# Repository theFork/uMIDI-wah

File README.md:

# uMIDI-wah

An optical guitar wah circuit based on the weeping demon circuit

* Uses [uMIDI](https://github.com/theFork/uMIDI) for control, MIDI and USB communication
* Optical wah control using a PWM

## uMIDI attachment
In order to be able to mount a uMIDI on top of the board, the three uMIDI GPIO connectors (boxed headers) have to be placed on its bottom side. Also, a male pin header row (1x10 pins, 2.54mm) has to be soldered to the MIDI and power section of the uMIDI module (also bottom side).

Another option would be to attach the uMIDI below the wah PCBA. In this case, the connectors have to side on the top side of the PCB.

In both cases, female headers are required for the wah PCBA:

* 3x Female header 2x5 pins, 2.54mm (i.e. TE 215307-5)
* 1x Female header 1x10 pins, 2.54mm (i.e. TE 1-215297-0)

## EDA
* Requires KiCad 8.x.x

## Ressources
Many of this is based on the work of Chet Gnegy: https://ccrma.stanford.edu/~chet/projects/weepingdemon.html

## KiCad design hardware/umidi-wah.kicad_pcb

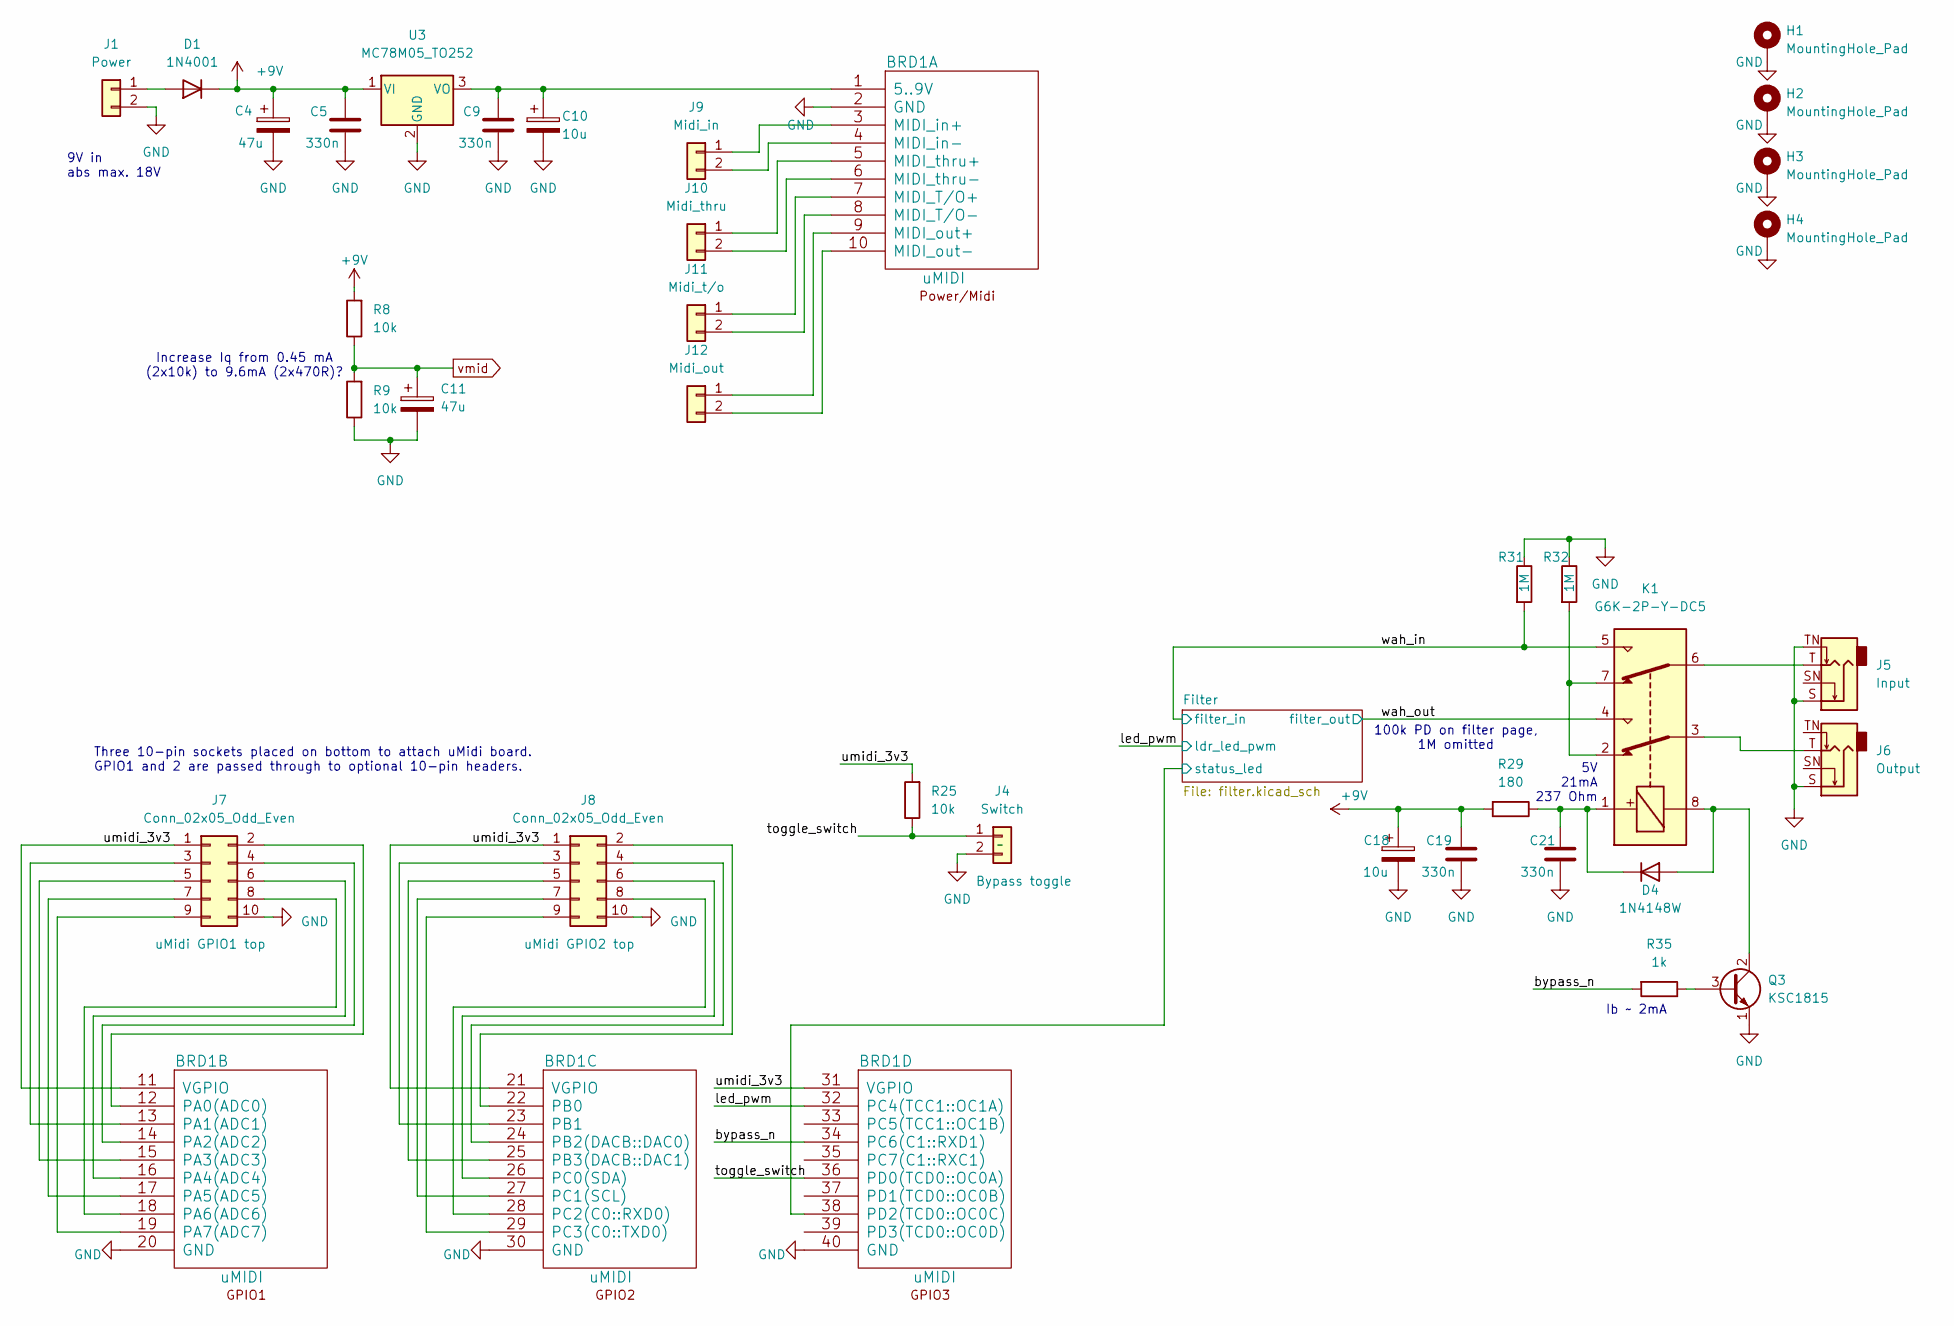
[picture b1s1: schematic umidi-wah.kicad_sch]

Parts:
BRD1: uMIDI; uMIDI_faceup
C4, C11: 47u; C_1206_3216Metric_Pad1.33x1.80mm_HandSolder
C5, C9, C19, C21: 330n; C_0805_2012Metric_Pad1.18x1.45mm_HandSolder
C10, C18: 10u; C_1206_3216Metric_Pad1.33x1.80mm_HandSolder
D1: 1N4001; D_DO-41_SOD81_P10.16mm_Horizontal
D4: 1N4148W; D_SOD-123
H1, H2, H3, H4: MountingHole_Pad; MountingHole_3.2mm_M3_Pad
J1: Power; SolderWire-1sqmm_1x02_P5.4mm_D1.4mm_OD2.7mm
J4: Switch; SolderWire-1sqmm_1x02_P5.4mm_D1.4mm_OD2.7mm
J5: Input; Jack_6.35mm_Neutrik_NMJ4HCD2_Horizontal
J6: Output; Jack_6.35mm_Neutrik_NMJ4HCD2_Horizontal
J7, J8: Conn_02x05_Odd_Even; IDC-Header_2x05_P2.54mm_Vertical
J9: Midi_in; SolderWire-1sqmm_1x02_P5.4mm_D1.4mm_OD2.7mm
J10: Midi_thru; SolderWire-1sqmm_1x02_P5.4mm_D1.4mm_OD2.7mm
J11: Midi_t/o; SolderWire-1sqmm_1x02_P5.4mm_D1.4mm_OD2.7mm
J12: Midi_out; SolderWire-1sqmm_1x02_P5.4mm_D1.4mm_OD2.7mm
K1: G6K-2P-Y-DC5; Relay_DPDT_Omron_G6K-2P-Y; Manufacturer Part Number G6K-2P-Y-DC5
Q3: KSC1815; TO-92; Manufacturer Part Number KSC1815
R8, R9, R25: 10k; R_0805_2012Metric_Pad1.20x1.40mm_HandSolder
R29: 180; R_0805_2012Metric_Pad1.20x1.40mm_HandSolder
R31, R32: 1M; R_0805_2012Metric_Pad1.20x1.40mm_HandSolder
R35: 1k; R_0805_2012Metric_Pad1.20x1.40mm_HandSolder
U3: MC78M05_TO252; TO-252-2; Manufacturer Part Number MC78M05CD

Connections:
+9V: C4.1, C5.1, C18.1, C19.1, D1.1 (K), R8.2, R29.2, U3.1 (VI); also elsewhere on the board
/Filter/status_led: BRD1.38 (PD2(TCD0::OC0C)); also elsewhere on the board
/bypass_n: BRD1.34 (PC6(C1::RXD1)), R35.2
/led_pwm: BRD1.32 (PC4(TCC1::OC1A)); also elsewhere on the board
/toggle_switch: BRD1.36 (PD0(TCD0::OC0A)), J4.1, R25.1
/umidi_3v3: BRD1.11 (VGPIO), BRD1.21 (VGPIO), BRD1.31 (VGPIO), J7.1, J8.1, R25.2
/wah_in: K1.5, R31.2; also elsewhere on the board
/wah_out: K1.4; also elsewhere on the board
GND: BRD1.2 (GND), BRD1.20 (GND), BRD1.30 (GND), BRD1.40 (GND), C4.2, C5.2, C9.2, C10.2, C11.2, C18.2, C19.2, C21.2, H1.1, H2.1, H3.1, H4.1, J1.2, J4.2, J5.S, J5.TN, J6.S, J7.10, J8.10, Q3.1 (E), R9.1, R31.1, R32.1, U3.2 (GND); also elsewhere on the board
unnamed: BRD1.1 (5..9V), C9.1, C10.1, U3.3 (VO)
unnamed: BRD1.7 (MIDI_T/O+), J11.1
unnamed: BRD1.8 (MIDI_T/O-), J11.2
unnamed: BRD1.3 (MIDI_in+), J9.1
unnamed: BRD1.4 (MIDI_in-), J9.2
unnamed: BRD1.9 (MIDI_out+), J12.1
unnamed: BRD1.10 (MIDI_out-), J12.2
unnamed: BRD1.5 (MIDI_thru+), J10.1
unnamed: BRD1.6 (MIDI_thru-), J10.2
unnamed: BRD1.12 (PA0(ADC0)), J7.2
unnamed: BRD1.13 (PA1(ADC1)), J7.3
unnamed: BRD1.14 (PA2(ADC2)), J7.4
unnamed: BRD1.15 (PA3(ADC3)), J7.5
unnamed: BRD1.16 (PA4(ADC4)), J7.6
unnamed: BRD1.17 (PA5(ADC5)), J7.7
unnamed: BRD1.18 (PA6(ADC6)), J7.8
unnamed: BRD1.19 (PA7(ADC7)), J7.9
unnamed: BRD1.22 (PB0), J8.2
unnamed: BRD1.23 (PB1), J8.3
unnamed: BRD1.24 (PB2(DACB::DAC0)), J8.4
unnamed: BRD1.25 (PB3(DACB::DAC1)), J8.5
unnamed: BRD1.26 (PC0(SDA)), J8.6
unnamed: BRD1.27 (PC1(SCL)), J8.7
unnamed: BRD1.28 (PC2(C0::RXD0)), J8.8
unnamed: BRD1.29 (PC3(C0::TXD0)), J8.9
unnamed: D1.2 (A), J1.1
unnamed: D4.2 (A), K1.8, Q3.2 (C)
unnamed: C21.1, D4.1 (K), K1.1, R29.1
unnamed: J5.T, K1.6
unnamed: J6.T, K1.3
unnamed: K1.2, K1.7, R32.2
unnamed: Q3.3 (B), R35.1
vmid: C11.1, R8.1, R9.2; also elsewhere on the board

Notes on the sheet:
Increase Iq from 0.45 mA (2x10k) to 9.6mA (2x470R)?
9V in abs max. 18V
Ib ~ 2mA
Three 10-pin sockets placed on bottom to attach uMidi board. GPIO1 and 2 are passed through to optional 10-pin headers.
100k PD on filter page, 1M omitted
5V 21mA 237 Ohm

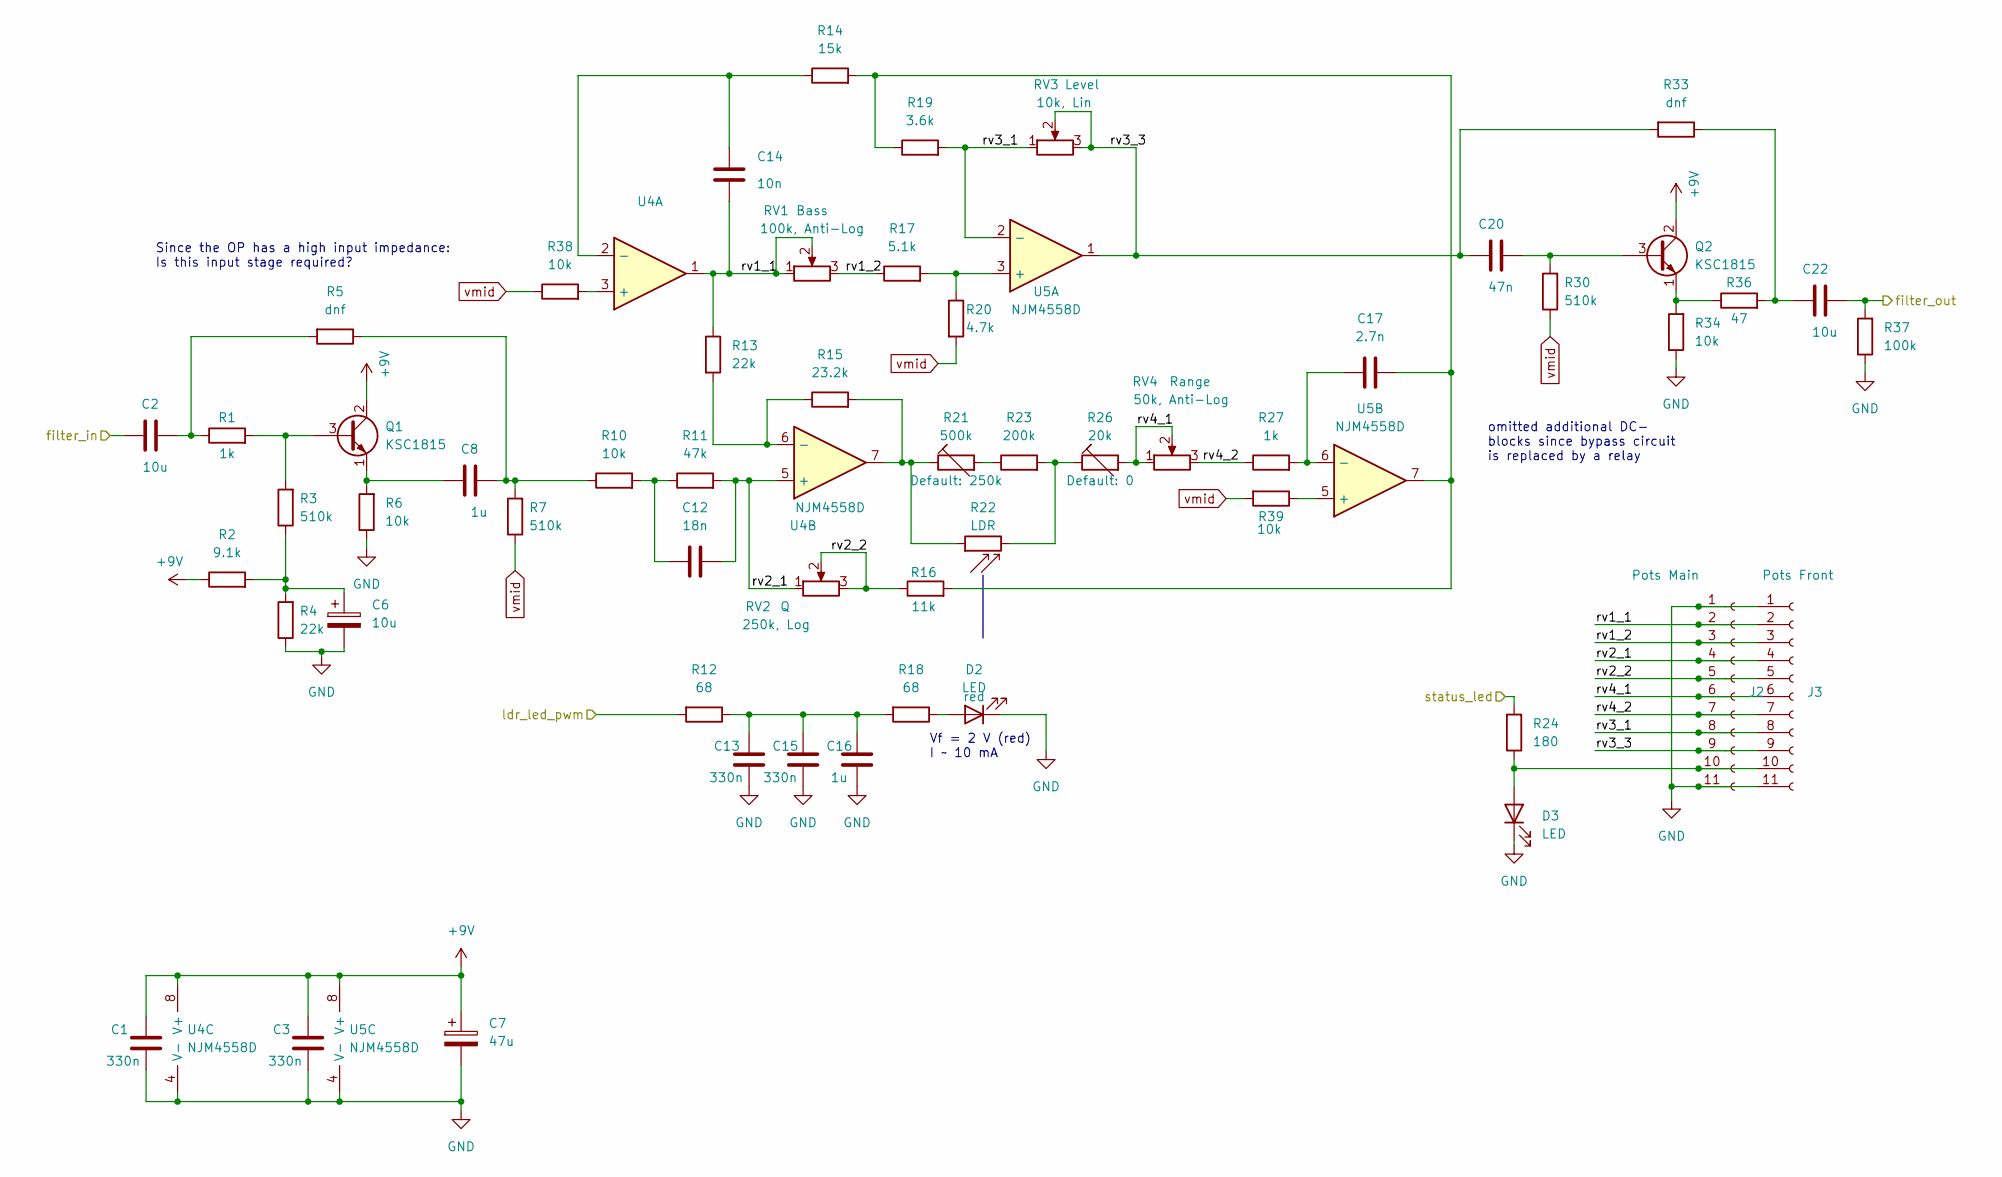
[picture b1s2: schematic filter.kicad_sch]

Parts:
C1, C3, C13, C15: 330n; C_0805_2012Metric_Pad1.18x1.45mm_HandSolder
C2, C22: 10u; C_Rect_L7.2mm_W11.0mm_P5.00mm_FKS2_FKP2_MKS2_MKP2
C6: 10u; C_1206_3216Metric_Pad1.33x1.80mm_HandSolder
C7: 47u; C_1206_3216Metric_Pad1.33x1.80mm_HandSolder
C8: 1u; C_Rect_L4.6mm_W5.5mm_P2.50mm_MKS02_FKP02
C12: 18n; C_Rect_L7.0mm_W2.5mm_P5.00mm
C14: 10n; C_Rect_L4.6mm_W5.5mm_P2.50mm_MKS02_FKP02; Manufacturer Part Number MKS0C021000B00JSSD
C16: 1u; C_0805_2012Metric_Pad1.18x1.45mm_HandSolder
C17: 2.7n; C_Rect_L7.0mm_W2.5mm_P5.00mm
C20: 47n; C_Rect_L4.6mm_W5.5mm_P2.50mm_MKS02_FKP02; Manufacturer Part Number MKS0C024700B00JSSD
D2, D3: LED; LED_D5.0mm
J2: Pots Main; PinHeader_1x11_P2.54mm_Vertical
J3: Pots Front; PinHeader_1x11_P2.54mm_Vertical
Q1, Q2: KSC1815; TO-92; Manufacturer Part Number KSC1815
R1, R27: 1k; R_0805_2012Metric_Pad1.20x1.40mm_HandSolder
R2: 9.1k; R_0805_2012Metric_Pad1.20x1.40mm_HandSolder
R3, R7, R30: 510k; R_0805_2012Metric_Pad1.20x1.40mm_HandSolder
R4, R13: 22k; R_0805_2012Metric_Pad1.20x1.40mm_HandSolder
R5, R33: dnf; R_0805_2012Metric_Pad1.20x1.40mm_HandSolder
R6, R10, R34, R38, R39: 10k; R_0805_2012Metric_Pad1.20x1.40mm_HandSolder
R11: 47k; R_0805_2012Metric_Pad1.20x1.40mm_HandSolder
R12, R18: 68; R_0805_2012Metric_Pad1.20x1.40mm_HandSolder
R14: 15k; R_0805_2012Metric_Pad1.20x1.40mm_HandSolder
R15: 23.2k; R_0805_2012Metric_Pad1.20x1.40mm_HandSolder
R16: 11k; R_0805_2012Metric_Pad1.20x1.40mm_HandSolder
R17: 5.1k; R_0805_2012Metric_Pad1.20x1.40mm_HandSolder
R19: 3.6k; R_0805_2012Metric_Pad1.20x1.40mm_HandSolder
R20: 4.7k; R_0805_2012Metric_Pad1.20x1.40mm_HandSolder
R21: 500k; Potentiometer_Piher_PT-10-V10_Vertical_Hole; Manufacturer Part Number PT10LV10-504A2020
R22: LDR; R_LDR_4.9x4.2mm_P2.54mm_Vertical; Manufacturer Part Number PDV P9004 or PDV 9203
R23: 200k; R_0805_2012Metric_Pad1.20x1.40mm_HandSolder
R24: 180; R_0805_2012Metric_Pad1.20x1.40mm_HandSolder
R26: 20k; Potentiometer_Piher_PT-10-V10_Vertical_Hole; Manufacturer Part Number PT10LV10-203A2020
R36: 47; R_0805_2012Metric_Pad1.20x1.40mm_HandSolder
R37: 100k; R_0805_2012Metric_Pad1.20x1.40mm_HandSolder
RV1: 100k, Anti-Log; Potentiometer_Alpha_RV16AF-20-15k-Single_Horizontal; Manufacturer Part Number RV16AF-20-15K-C100K
RV2: 250k, Log; Potentiometer_Alpha_RV16AF-20-15k-Single_Horizontal; Manufacturer Part Number RV16AF-20-15K-A250K
RV3: 10k, Lin; Potentiometer_Alpha_RV16AF-20-15k-Single_Horizontal; Manufacturer Part Number RV16AF-20-15K-B10K
RV4: 50k, Anti-Log; Potentiometer_Alpha_RV16AF-20-15k-Single_Horizontal; Manufacturer Part Number RV16AF-20-15K-C50K
U4, U5: NJM4558D; DIP-8_W7.62mm_Socket_LongPads; Manufacturer Part Number NJM4558D

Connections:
+9V: C1.1, C3.1, C7.1, Q1.2 (C), Q2.2 (C), R2.1, U4.8 (V+), U5.8 (V+); also elsewhere on the board
/Filter/rv1_1: C14.2, J2.2, J3.2, R13.1, RV1.1, RV1.2, U4.1
/Filter/rv1_2: J2.3, J3.3, R17.1, RV1.3
/Filter/rv2_1: C12.2, J2.4, J3.4, R11.2, RV2.1, U4.5 (+)
/Filter/rv2_2: J2.5, J3.5, R16.1, RV2.2, RV2.3
/Filter/rv3_1: J2.8, J3.8, R19.2, RV3.1, U5.2 (-)
/Filter/rv3_3: C20.1, J2.9, J3.9, R33.2, RV3.2, RV3.3, U5.1
/Filter/rv4_1: J2.6, J3.6, R26.2, RV4.1, RV4.2
/Filter/rv4_2: J2.7, J3.7, R27.1, RV4.3
/Filter/status_led: R24.2; also elsewhere on the board
/led_pwm: R12.2; also elsewhere on the board
/wah_in: C2.1; also elsewhere on the board
/wah_out: C22.2, R37.2; also elsewhere on the board
GND: C1.2, C3.2, C6.2, C7.2, C13.2, C15.2, C16.2, D2.1 (K), D3.1 (K), J2.1, J2.11, J3.1, J3.11, R4.1, R6.1, R34.1, R37.1, U4.4 (V-), U5.4 (V-); also elsewhere on the board
unnamed: C2.2, R1.1, R5.2
unnamed: C6.1, R2.2, R3.1, R4.2
unnamed: C8.2, R5.1, R7.2, R10.1
unnamed: C12.1, R10.2, R11.1
unnamed: C13.1, C15.1, C16.1, R12.1, R18.2
unnamed: C17.2, R14.2, R16.2, R19.1, U5.7
unnamed: C22.1, R33.1, R36.2
unnamed: D2.2 (A), R18.1
unnamed: D3.2 (A), J2.10, J3.10, R24.1
unnamed: Q1.3 (B), R1.2, R3.2
unnamed: C8.1, Q1.1 (E), R6.2
unnamed: C20.2, Q2.3 (B), R30.2
unnamed: Q2.1 (E), R34.2, R36.1
unnamed: R15.2, R21.1, R22.1, U4.7
unnamed: R21.2, R23.1
unnamed: R22.2, R23.2, R26.1
unnamed: R38.2, U4.3 (+)
unnamed: C14.1, R14.1, U4.2 (-)
unnamed: R13.2, R15.1, U4.6 (-)
unnamed: R17.2, R20.1, U5.3 (+)
unnamed: R39.1, U5.5 (+)
unnamed: C17.1, R27.2, U5.6 (-)
vmid: R7.1, R20.2, R30.1, R38.1, R39.2; also elsewhere on the board

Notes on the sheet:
omitted additional DC- blocks since bypass circuit is replaced by a relay
Vf = 2 V (red) I ~ 10 mA
Since the OP has a high input impedance: Is this input stage required?

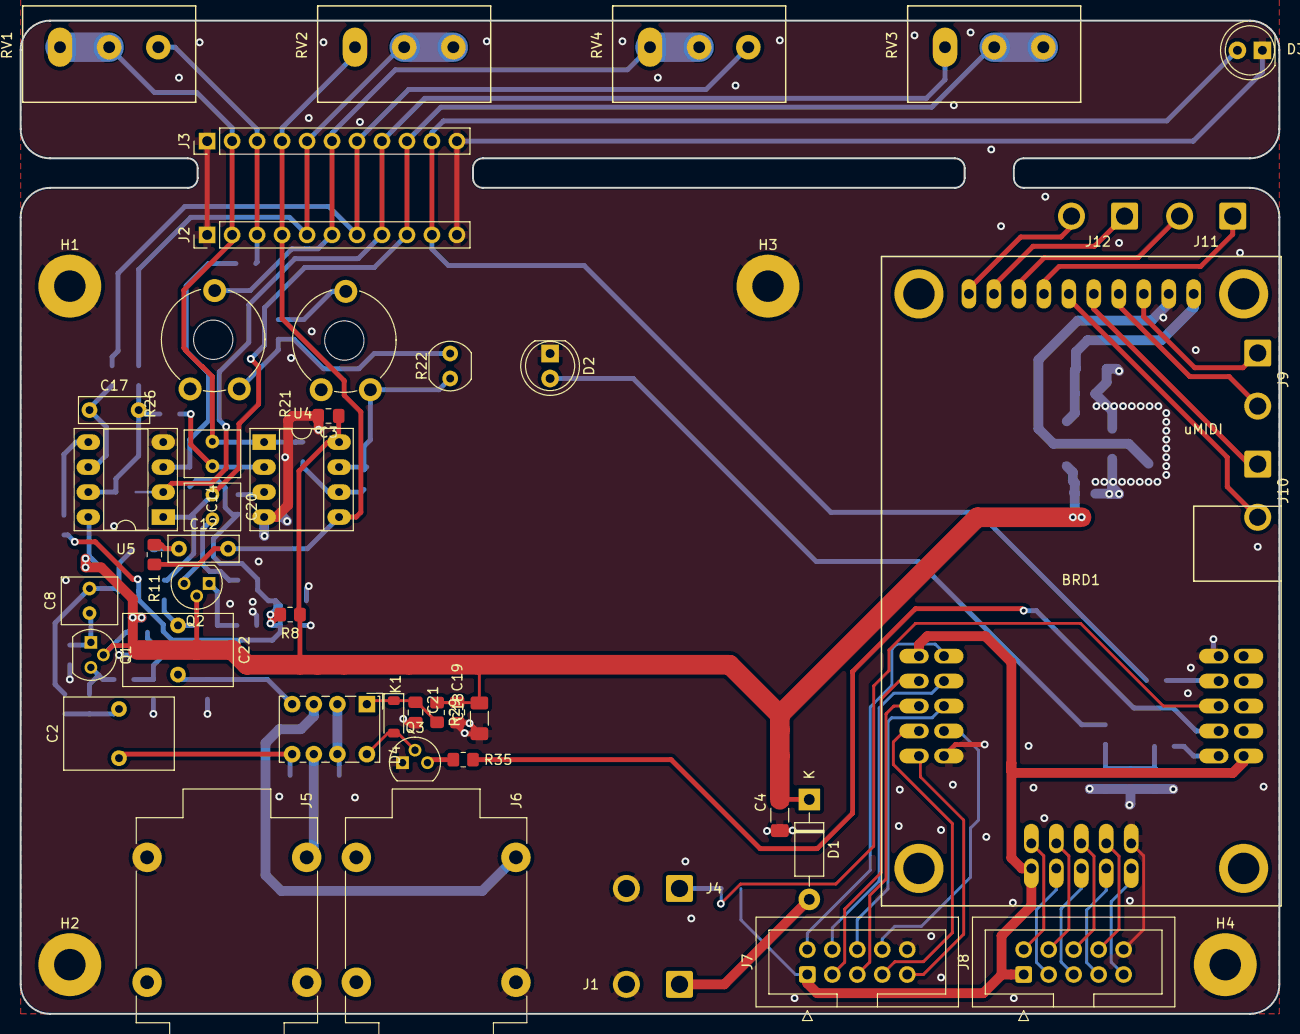
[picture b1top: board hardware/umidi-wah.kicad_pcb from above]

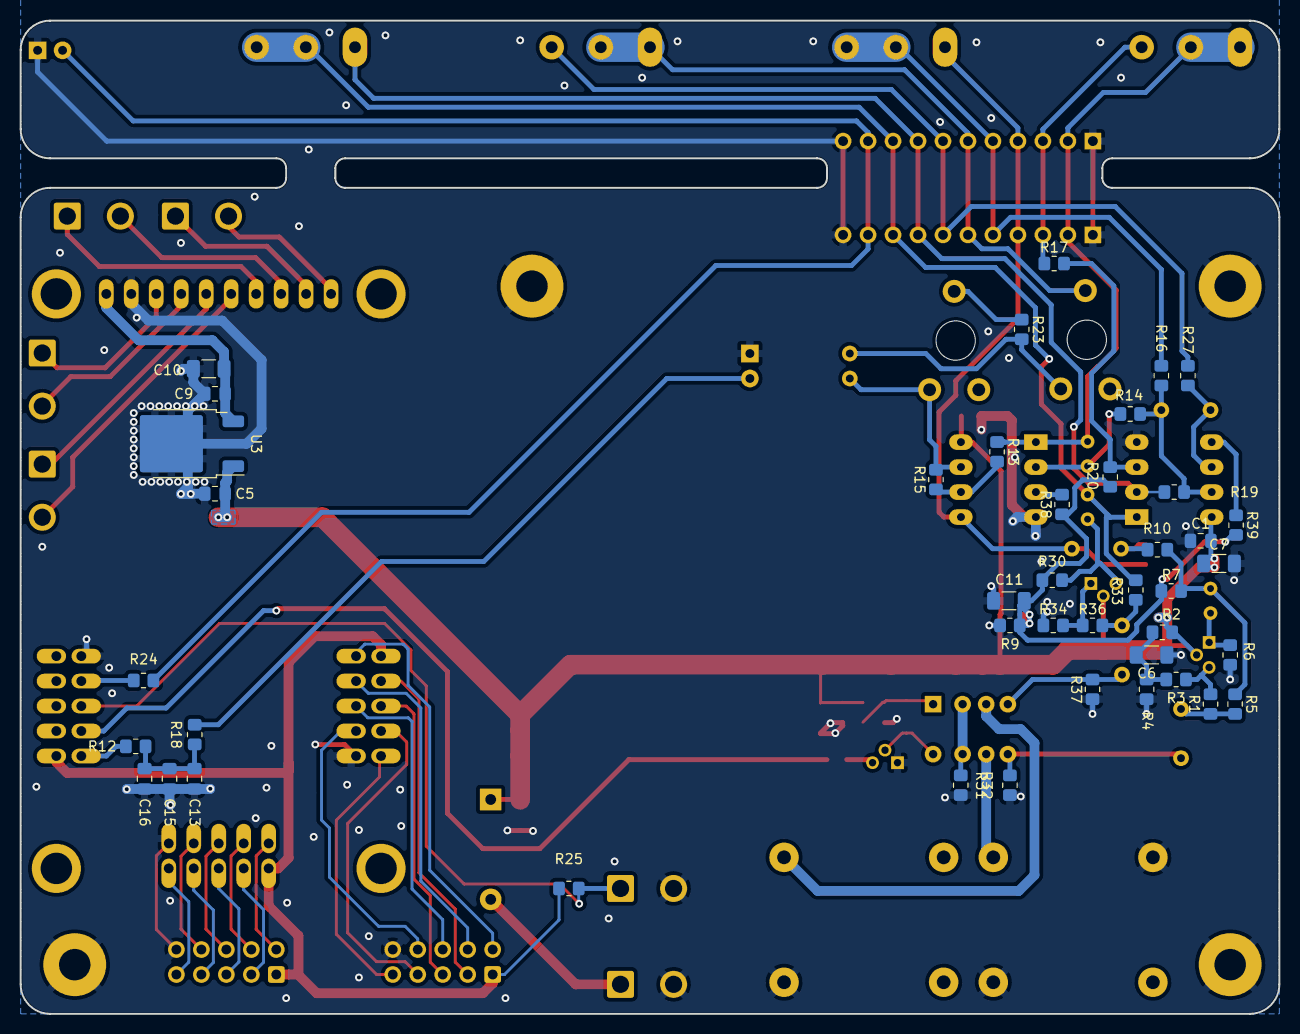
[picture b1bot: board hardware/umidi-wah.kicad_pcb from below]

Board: 2 copper layers, 128.0 x 101.0 mm, 92 parts (42 on the bottom side), 72 nets.

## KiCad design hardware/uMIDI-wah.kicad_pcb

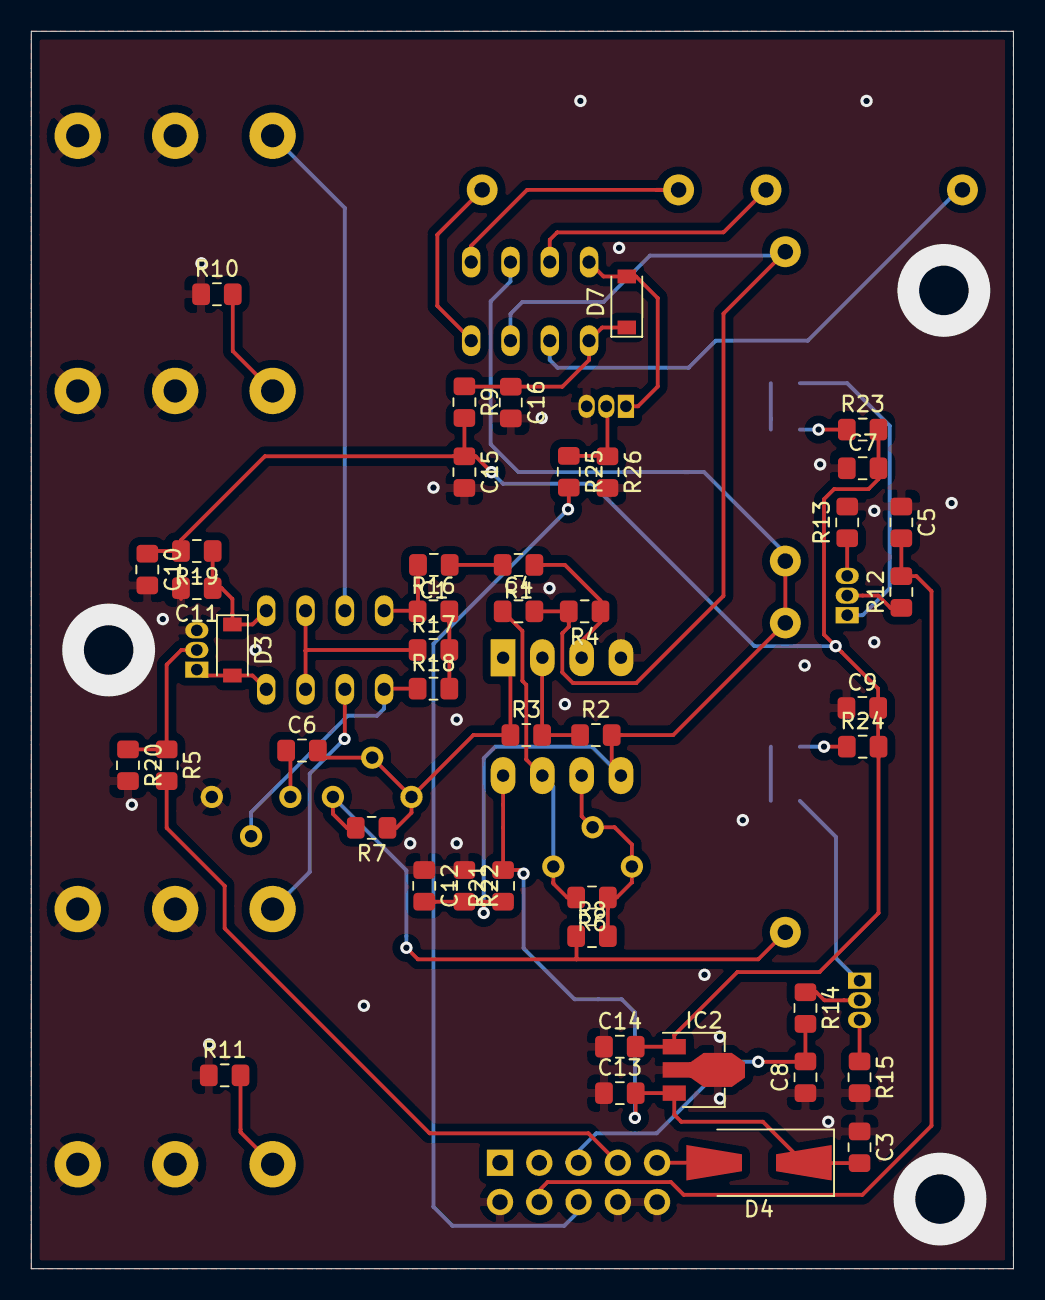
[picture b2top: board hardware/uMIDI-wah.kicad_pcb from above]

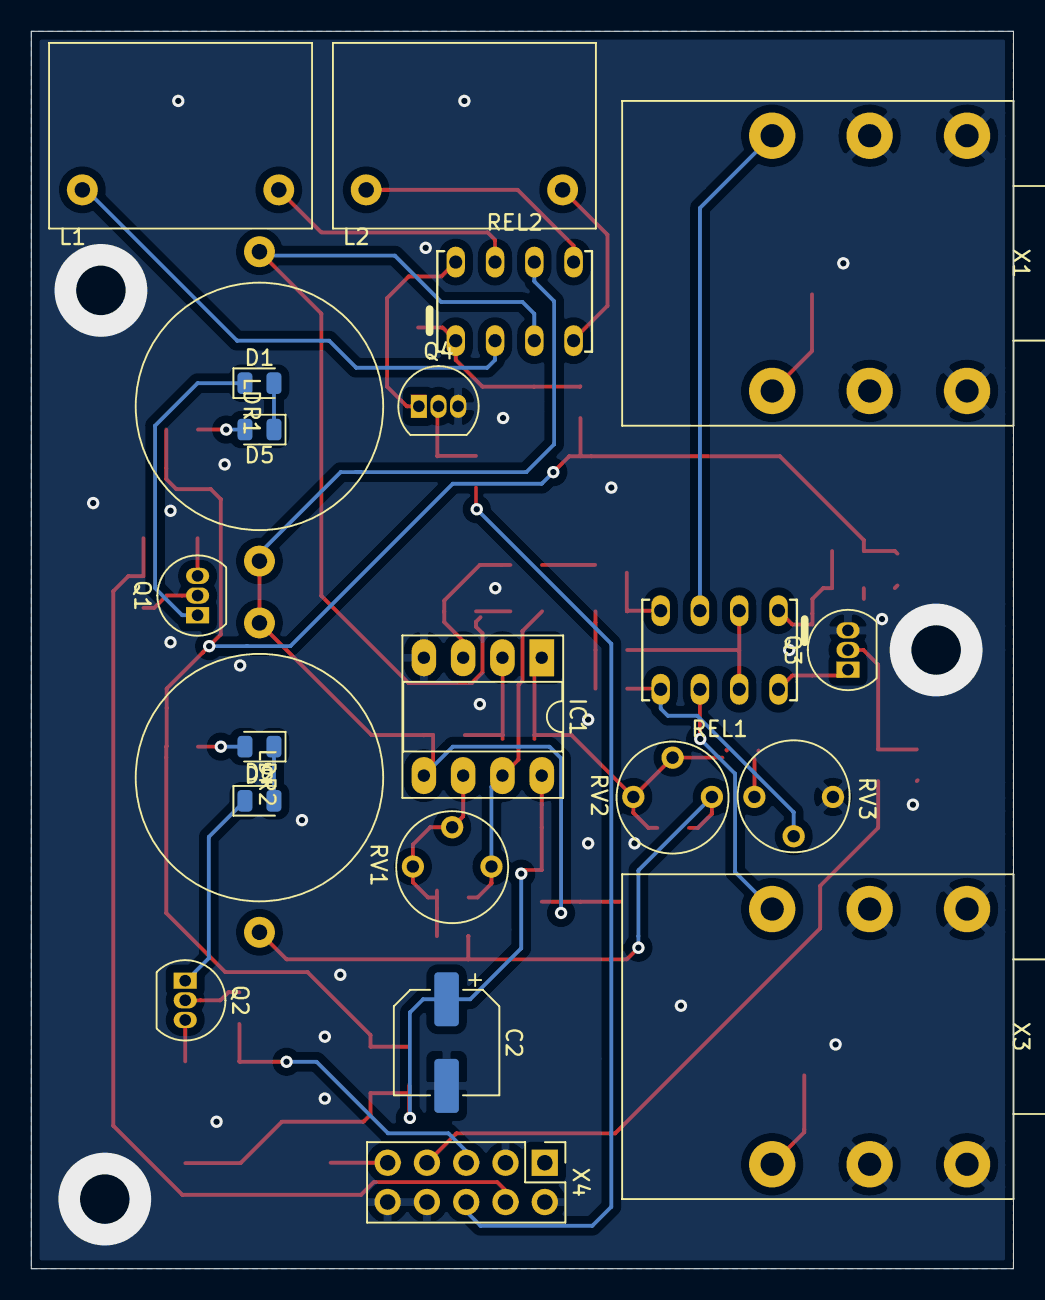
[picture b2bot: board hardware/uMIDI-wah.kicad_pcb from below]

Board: 2 copper layers, 63.5 x 80.0 mm, 67 parts (22 on the bottom side), 46 nets.

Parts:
C1, C6, C12: 22u; C_0805_2012Metric_Pad1.15x1.40mm_HandSolder
C2: 100u, 50V; CP_Elec_6.3x9.9
C3, C7, C9, C10, C11, C13, C14, C15, C16: 100n; C_0805_2012Metric_Pad1.15x1.40mm_HandSolder
C4: 33n; C_0805_2012Metric_Pad1.15x1.40mm_HandSolder
C5, C8: 10u; C_0805_2012Metric_Pad1.15x1.40mm_HandSolder
D1, D2, D5, D6: LED; LED_0805_2012Metric
D3, D7: 1N4148; D_SOD-123
D4: D; D_SMA-SMB_Universal_Handsoldering
IC1: Opamp_Dual_Generic; DIP-8_W7.62mm_Socket_LongPads
IC2: L78L09_SOT89; SOT-89-3
L1: Fasel Red; Fasel
L2: Fasel Yellow; Fasel
LDR1, LDR2: NORPS-12; LDR reverse mount
Q1, Q2, Q3, Q4: BC547; TO-92_Inline
R1, R3, R8, R21, R22: 100k; R_0805_2012Metric_Pad1.15x1.40mm_HandSolder
R2, R4, R5, R12, R14, R23, R24, R25: 1k; R_0805_2012Metric_Pad1.15x1.40mm_HandSolder
R6, R7: dnf; R_0805_2012Metric_Pad1.15x1.40mm_HandSolder
R9, R19: 180; R_0805_2012Metric_Pad1.15x1.40mm_HandSolder
R10, R11, R16, R17, R18, R20, R26: 100M; R_0805_2012Metric_Pad1.15x1.40mm_HandSolder
R13, R15: 0; R_0805_2012Metric_Pad1.15x1.40mm_HandSolder
REL1, REL2: Omron G6K-2P-5VCD; Omron_G6K-2P
RV1, RV2, RV3: 470k; Potentiometer_Vishay_T7-YA_Single_Vertical
X1, X3: AudioJack3_Switch; AudioJack 6.3mm Stereo
X4: Conn_01x10; PinHeader_2x05_P2.54mm_Vertical

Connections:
/+9V: C7.2, C9.2, C10.1, C14.2, C15.1, IC2.1, R9.2, R19.2, R23.2, R24.2
/Bypass/FX_Send: C1.2, R16.1, REL1.4
/Bypass/Loop_In: REL1.3, X1.T
/Bypass/Loop_Out: REL1.6, X3.T
/Bypass/bypass: R17.1, REL1.2, REL1.7
/Bypass/relais_n: D3.2, Q3.1, REL1.8
/Bypass/relais_p: C11.1, D3.1, R19.1, REL1.1
/Fasel: R25.2, X4.6
/Inductor/relais_n: D7.2, Q4.1, REL2.8
/Inductor/relais_p: C16.1, D7.1, R9.1, REL2.1
/PWM_Q: C5.2, R12.2, X4.4
/PWM_Wah: C8.2, R14.2, X4.5
/VDDa: C2.1, C3.2, C13.2, D4.1, IC1.8, IC2.3, R21.2
/Vref: C12.2, IC1.5, LDR1.2, LDR2.2, R2.2, R21.1, R22.2, REL2.6
/bypass_n: R5.2, X4.7
/in_dc: C1.1, R1.2
/out: R18.1, REL1.5, RV3.2
/q: C4.2, LDR1.1, R4.2, REL2.3
/wah: LDR2.1, R7.2, R8.1, RV2.1
GND: C2.2, C3.1, C5.1, C7.1, C8.1, C9.1, C10.2, C11.2, C12.1, C13.1, C14.1, C15.2, C16.2, IC1.4, IC2.2, Q3.3, Q4.3, R10.1, R11.1, R13.2, R15.2, R20.2, R22.1, R26.2, RV3.3, X1.R, X1.RN, X1.S, X1.SN, X3.R, X3.RN, X3.S, X3.SN, X4.2, X4.3, X4.8, X4.10
GNDA: R16.2, R17.2, R18.2
unnamed: C4.1, IC1.7, R6.2, RV1.1
unnamed: C6.1, RV3.1
unnamed: C6.2, IC1.1, R3.1, R7.1, RV2.2, RV2.3
unnamed: D1.1, Q1.1
unnamed: D1.2, D5.1
unnamed: D2.1, Q2.1
unnamed: D2.2, D6.1
unnamed: D4.2, X4.9
unnamed: D5.2, R23.1
unnamed: D6.2, R24.1
unnamed: IC1.2, R2.1, R3.2
unnamed: IC1.3, R1.1, R4.1
unnamed: IC1.6, R6.1, R8.2, RV1.2, RV1.3
unnamed: L1.1, REL2.2
unnamed: L1.2, REL2.7
unnamed: L2.1, REL2.5
unnamed: L2.2, REL2.4
unnamed: Q1.2, R12.1
unnamed: Q1.3, R13.1
unnamed: Q2.2, R14.1
unnamed: Q2.3, R15.1
unnamed: Q3.2, R5.1, R20.1
unnamed: Q4.2, R25.1, R26.1
unnamed: R10.2, X1.TN
unnamed: R11.2, X3.TN

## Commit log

2015-10-26 Remove rescue lib dependency; Join gnd and gnda
2015-10-26 Select trimmer and footprint
2015-10-26 Fix relay footprint
2015-10-26 Assign remaining footprints
2015-10-26 Start placement and routing
2015-10-26 Continue placement/routing
2015-11-01 Fix RV1 bom fields
2015-11-01 Add capacitor bom fields
2015-11-01 Add ldr bom fields; Change footprint
2015-11-01 Place and route
2015-11-01 Add resistor bom fields
2015-11-02 Add filter circuit to the pwm led
2015-11-09 Replace opamp uA741 by TL071
2015-12-04 DRC clean
2015-12-04 Increase pad size of ribbon connector
2015-12-04 Draw dimensions
2015-12-05 Fix SOIC package width
2015-12-05 Add readme
2016-01-22 Add ltspice simulation
2016-01-23 Simulation: Modify C2 and C5; Add output scaler
2016-01-23 Fix 470k resistor supplier link
2016-01-23 Ignore simulation results
2016-01-23 Fix C9 supplier link
2016-01-23 Change C7 and C11; Adapt supplier links
2016-01-23 Constrain volume pot range
2016-01-23 Increase pcb size; Add label
2016-01-24 Increase trace widths
2016-01-30 Add and include uMIDI.pretty submodule
2016-01-30 Add 9V polarity protection diode
2016-02-21 Increase LDR pad size
2019-03-13 Fix readme
2019-03-17 Import wah schematic from simulation into KiCad
2019-03-17 Add QUCS simulation of v1.0 wah circuit
2019-03-17 Add LED drivers
2019-03-17 Reference Small Bear and R. G. Keen's arcticles on wah technology
2019-05-04 Edit eval schematic; Import bypass
2019-05-04 Annotate schematic
2019-05-04 Use 0805 footprint for all resistors
2019-05-04 Use 0805 footprint for all capacitors
2019-05-09 Add seconde fasel and Vref circuit
2019-05-09 Select and set all pots to 470k
2019-05-09 Add footprints and part info for IC and inductors
2019-05-09 Copy "official" .gitignore
2019-05-11 Create footprint for audio jacks
2019-05-11 Create footprint for LDRs
2019-05-11 Select and update LED circuit
2019-05-11 Assign footprints; add led supply circuit
2019-05-18 Fix footprints
2019-05-18 Initial placement and bom optimization
2019-05-21 Complete initial placement
2019-05-21 Use second relay to switch between inductors
2020-02-02 Place & route
2020-03-08 Optimize place & route, add label and OSHW logo
2020-03-15 Add missing manufacturer links
2020-03-15 Ignore plain text BOM
2020-03-26 Revision BOM: Get low-tech parts from Reichelt
2020-05-16 Fix relais supply
2020-05-16 Add in-/output labels to audio jacks
2023-02-18 Update readme for the demon branch
2023-02-18 Wipe all kicad files
2023-02-18 Ignore zip files (used by kicad for auto backups)
2023-02-18 Draw filter circuit
2023-02-18 Add in/out buffers, loosely based on demon circuit
    Keeping in mind that we will use a relay true bypass. Thus, we omitted the jfets and some dc blocks.
2023-02-18 Add bypass circuit
2023-02-18 Add led and filter circuit
2023-02-19 Sketch umidi connection
2023-02-19 Add power input and 5v ldo for umidi supply
2023-02-19 Add buffer stage bypass resistors
    Can be assembled to bypass input or output buffer stages.
2023-02-19 Use gpio pinout from current uMidi wah app
2023-02-19 Add status led and toggle switch connector
2023-02-19 Convert led filter to T-type
    Use the same values for the caps as used in our prototype. Use 2x 68 ohms instead of 2x 100 ohms, since this still results in a quiet low led current (10mA)
2023-02-19 Add/show potentiometer function fields
2023-02-20 Annotate schematic, assign footprints for jacks
2023-03-03 Add KiCad version info to readme
2023-03-03 Use trim resistors for ldr tuning
2023-03-03 Define trimmer and ldr footprints; Add supply infos
2023-03-03 Add all uMidi pin sockets for mech stability
2023-03-06 Move filter circuit to designated sheet
2023-03-16 Add top pin headers
2023-03-16 Fix Opamps
2023-03-16 Add wire connectors for front panel with pots
2023-03-16 Assign all footprints
2023-03-16 Place filter circuit
2023-03-16 Add pcb outline and test milling layer
2023-03-18 Add umidi symbol and footprint from umidi repo
2023-03-18 Compact parts
2023-03-18 Add uMIDI footprint
2023-03-18 Connect power to uMidi module
2023-03-18 Add header description to umidi symbol; Update schematic
2023-03-18 Integrate umidi symbol (schematic only)
2023-03-18 Route filter circuit
2023-03-18 Route peripherals
2023-03-18 Add bourns poti footprint
2023-03-18 Swap pots in schematic (now including mounting pins)
2023-03-18 Route pretty much everything
2023-03-22 Fix range poti value; Fix poti directions; Specify taper types
2023-03-22 Select poti manufacturer and part numbers
2023-03-23 Draw potentiometer alpha RV16AF footprint
2023-03-23 Replace bourns potentiometers in schematic and board
2023-03-23 Add some supplier links and datasheets
2023-03-23 Add supplier link; Change footprint of 18n film cap
2023-03-23 Remove local settings file
    See also https://forum.kicad.info/t/new-project-file-format/23705
2023-03-23 Specify 2n7 foil cap; Use generic 2.5/5mm footprints
2023-03-23 Specify 47n cap
2023-04-01 Review PCB
2023-04-13 Add mounting holes. Ref #3
2023-04-22 Move uMIDI, optimize all the things
2023-04-22 Fix uMIDI footprint (remove silkscreen)
2023-04-22 Refine PCB outline, add slots
2024-04-30 Make C8 footprint more generic (2.5 or 5mm pin distance)
2024-05-03 Redesign 9V distribution
2024-05-03 Increase trace widths (and more brd optimization)
2024-05-03 Optimize routing of umidi-3,3v
2024-05-03 Add artwork to solder mask and copper
2024-05-03 Optimize audio signal path
2024-05-03 Add solder holes for midi signals
    Now, it is possible to make the entire umidi-pcba pluggable.
2024-05-05 Convert to kicad 8.0 file format
2024-05-05 Doc umidi pcba attachment
2024-05-17 Reduce pcb width to 128mm
2024-05-17 Shrink potentiometer board
2024-05-17 Add mounting holes for umidi module
2024-05-19 Rotate pwr connector (increase clearance to signal out)
2024-05-19 Replace gpio connectors by boxed headers
2024-05-19 Small tweaks -> DRC clean
    Fix typo in board name, move umidi slighty south
2024-06-18 Fix integrator positive input (is now vmid)
2024-06-18 Fix unintended filter_out signal union. Revise some placement.
2024-07-04 Change R20 value to 4k7
2024-07-04 Fix: Connect R20 low side to Vmid instead of GND
2026-02-26 WIP: Improve EMC. Move relais between in and output.
2026-02-27 Revise in- and output stage placement
2026-02-27 Re-route in/output stages
2026-02-27 Move filter circuit to the left as far as possible
2026-02-28 Increase pot distance to 30mm
2026-02-28 Almost finish routing
2026-03-02 Route all missing airwires
2026-03-02 Fix drc issues
2026-03-02 Move primary midi i/o to right edge (increase distance)
2026-03-06 Revise assembly plan
2026-04-14 Update to KiCAD 10; Set R15 from 23k to 23k2 (E96)
